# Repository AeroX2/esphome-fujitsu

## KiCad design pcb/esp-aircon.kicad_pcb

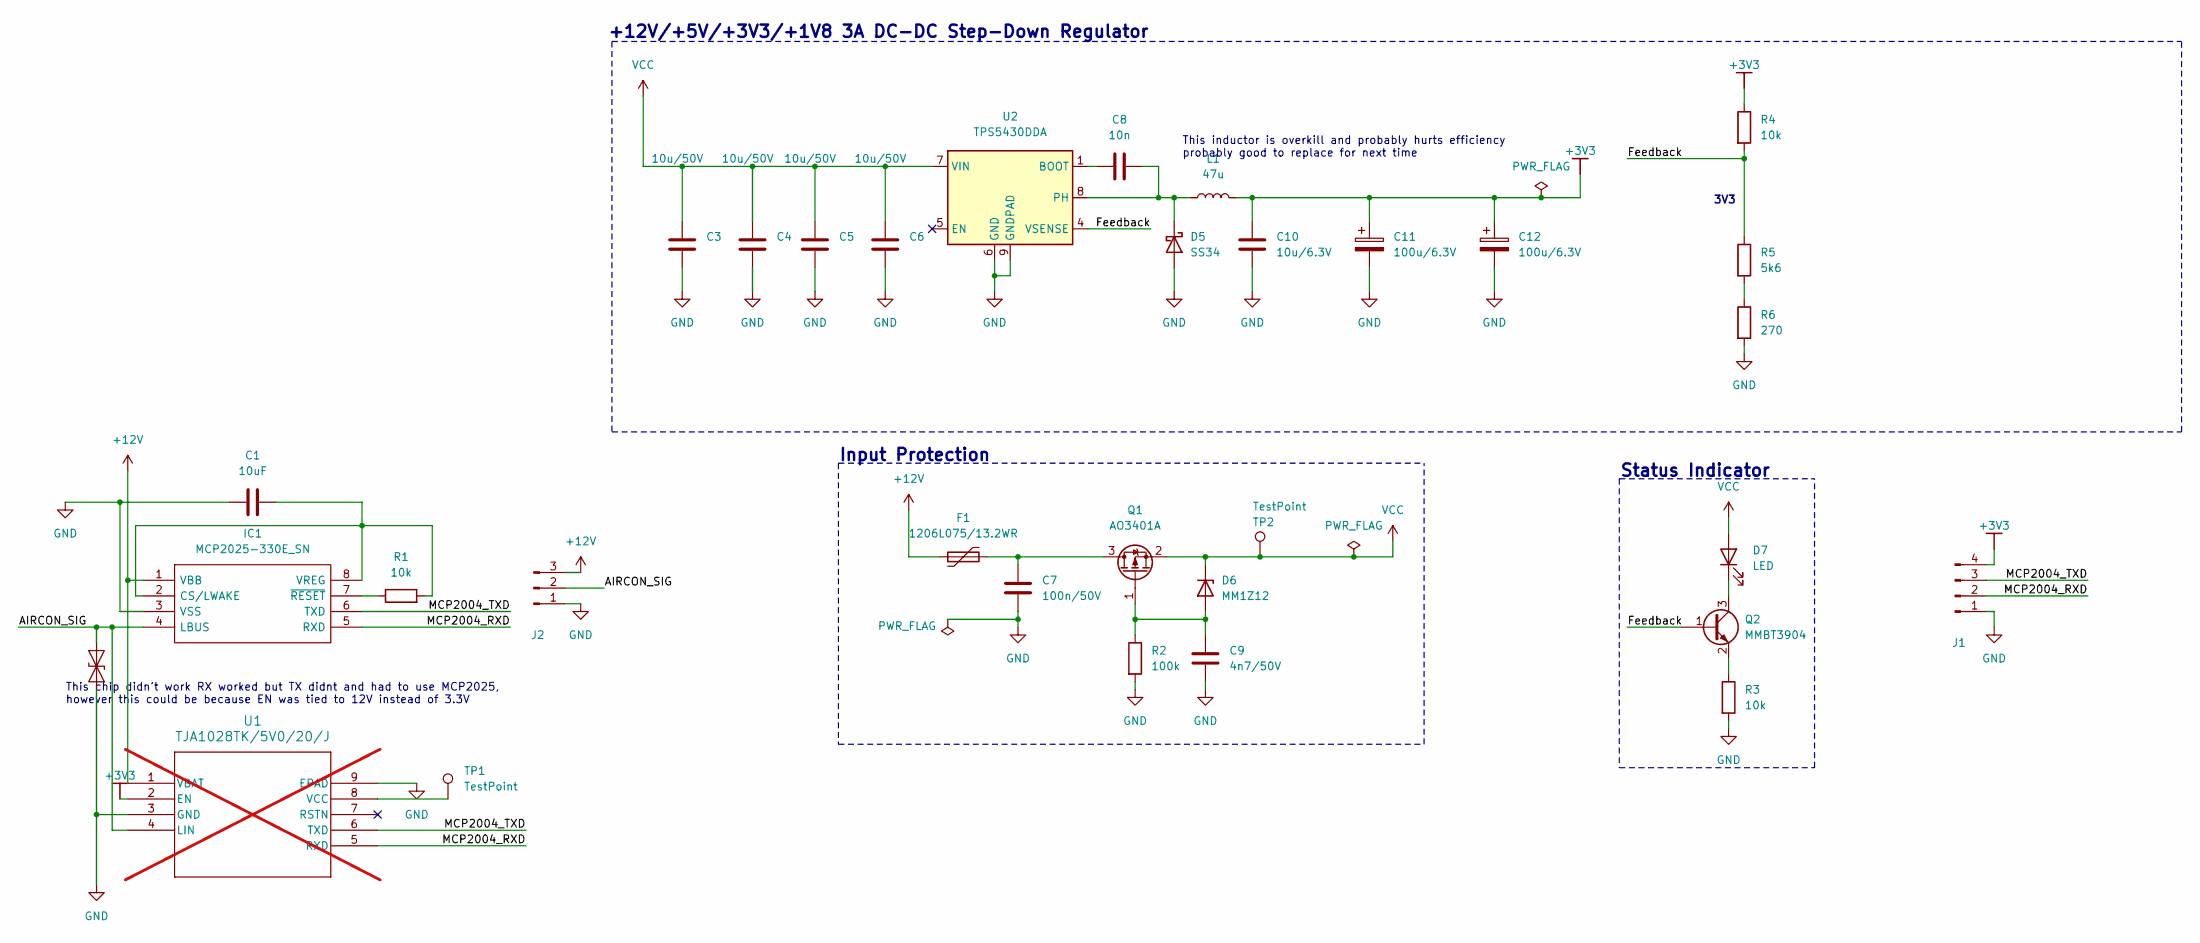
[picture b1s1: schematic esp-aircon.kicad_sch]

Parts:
C1: 10uF; C_1206_3216Metric
C3, C4, C5, C6: 10u/50V; C_1206_3216Metric; MPN CL31A106KBHNNNE; LCSC C13585
C7: 100n/50V; C_0603_1608Metric; MPN CC0603KRX7R9BB104; LCSC C14663
C8: 10n; C_0402_1005Metric; MPN CL05B103KB5NNNC; LCSC C15195
C9: 4n7/50V; C_0402_1005Metric; MPN 0402B472K500NT; LCSC C1538
C10: 10u/6.3V; C_0402_1005Metric; MPN CL05A106MQ5NUNC; LCSC C15525
C11, C12: 100u/6.3V; CP_EIA-3528-21_Kemet-B; MPN TAJB107K006RNJ; LCSC C16133
D1: PESD1IVN24; D_SOD-323
D5: SS34; D_SMA; MPN SS34; LCSC C8678
D6: MM1Z12; D_MiniMELF; MPN ZMM5V6; LCSC C8062
D7: LED; LED_0603_1608Metric; MPN 19-217/GHC-YR1S2/3T; LCSC C72043
F1: 1206L075/13.2WR; Fuse_1206_3216Metric; MPN 1206L300SLTHYR; LCSC C207041
IC1: MCP2025-330E_SN; SOIC127P600X175-8N; Manufacturer_Part_Number MCP2025-330E/SN; Mouser Part Number 579-MCP2025-330E/SN
J1: Conn_01x04_Pin; PinHeader_1x04_P2.54mm_Vertical
J2: Conn_01x03_Pin; PinHeader_1x03_P2.54mm_Vertical
L1: 47u; L_Sunlord_MWSA1004S_10x11.5x4mm; MPN MWSA1004S-470MT; LCSC C408491
Q1: AO3401A; SOT-23; MPN AO3401A; LCSC C15127
Q2: MMBT3904; SOT-23; MPN MMBT3904; LCSC C20526
R1: 10k; R_0402_1005Metric
R2: 100k; R_0402_1005Metric; MPN 0402WGF1003TCE; LCSC C25741
R3: 10k; R_0603_1608Metric; MPN 0603WAF1002T5E; LCSC C25804
R4: 10k; R_0402_1005Metric; MPN 0402WGF1002TCE; LCSC C25744
R5: 5k6; R_0603_1608Metric; MPN 0402WGF5601TCE; LCSC C25908
R6: 270; R_0603_1608Metric; MPN 0603WAF2700T5E; LCSC C22966
TP1, TP2: TestPoint; TestPoint_Pad_D1.5mm
U1: TJA1028TK/5V0/20/J; HVSON8_3X3_NXP; not fitted
U2: TPS5430DDA; TI_SO-PowerPAD-8_ThermalVias; MPN TPS5430DDAR; JLC LSOP-8_EP_3.9x4.9x1.27P

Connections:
+3V3: C10.1, C11.1, C12.1, J1.4, L1.2, R4.1, U1.2 (EN)
+12V: F1.1, IC1.1 (VBB), J2.3, U1.1 (VBAT)
/AIRCON_SIG: D1.2 (A2), IC1.4 (LBUS), J2.2, U1.4 (LIN)
/Feedback: Q2.1 (B), R4.2, R5.1, U2.4 (VSENSE)
/MCP2004_RXD: IC1.5 (RXD), J1.2, U1.5 (RXD)
/MCP2004_TXD: IC1.6 (TXD), J1.3, U1.6 (TXD)
GND: C1.1, C3.2, C4.2, C5.2, C6.2, C7.2, C9.2, C10.2, C11.2, C12.2, D1.1 (A1), D5.2 (A), IC1.3 (VSS), J1.1, J2.1, R2.2, R3.2, R6.2, U1.3 (GND), U1.9 (EPAD), U2.6 (GND), U2.9 (GNDPAD)
unnamed: C8.2, D5.1 (K), L1.1, U2.8 (PH)
unnamed: C9.1, D6.2 (A), Q1.1 (G), R2.1
unnamed: D7.1 (K), Q2.3 (C)
unnamed: C1.2, IC1.2 (CS/LWAKE), IC1.8 (VREG), R1.2
unnamed: IC1.7 (~RESET), R1.1
unnamed: C7.1, F1.2, Q1.3 (D)
unnamed: Q2.2 (E), R3.1
unnamed: R5.2, R6.1
unnamed: TP1.1, U1.8 (VCC)
unnamed: C8.1, U2.1 (BOOT)
VCC: C3.1, C4.1, C5.1, C6.1, D6.1 (K), D7.2 (A), Q1.2 (S), TP2.1, U2.7 (VIN)

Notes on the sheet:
Input Protection
This inductor is overkill and probably hurts efficiency probably good to replace for next time
3V3
Status Indicator
This chip didn't work RX worked but TX didnt and had to use MCP2025, however this could be because EN was tied to 12V instead of 3.3V
+12V/+5V/+3V3/+1V8 3A DC-DC Step-Down Regulator

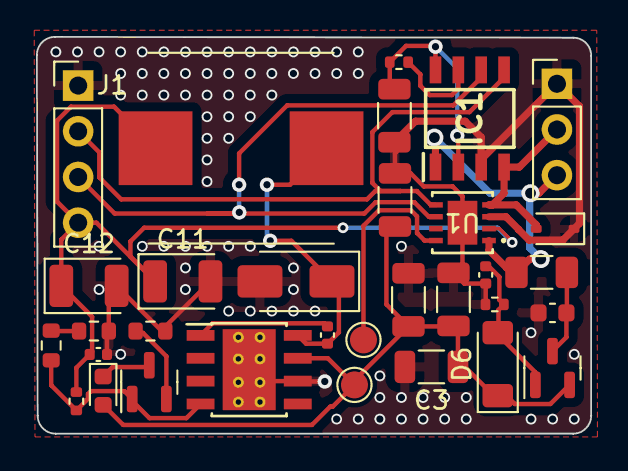
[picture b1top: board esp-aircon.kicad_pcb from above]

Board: 2 copper layers, 30.8 x 22.0 mm, 32 parts (0 on the bottom side), 18 nets.

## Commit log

2024-02-02 Finally got it working
2024-02-02 Add PCB
